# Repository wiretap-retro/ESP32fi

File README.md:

# ESP32fi
A parallel port ESP32 plipbox for the Amiga.

## Info
Do not build. Not tested, firmware and software still pending.

Built for use with the ImpBox32 project: https://github.com/AmigaPorts/ImpBox32

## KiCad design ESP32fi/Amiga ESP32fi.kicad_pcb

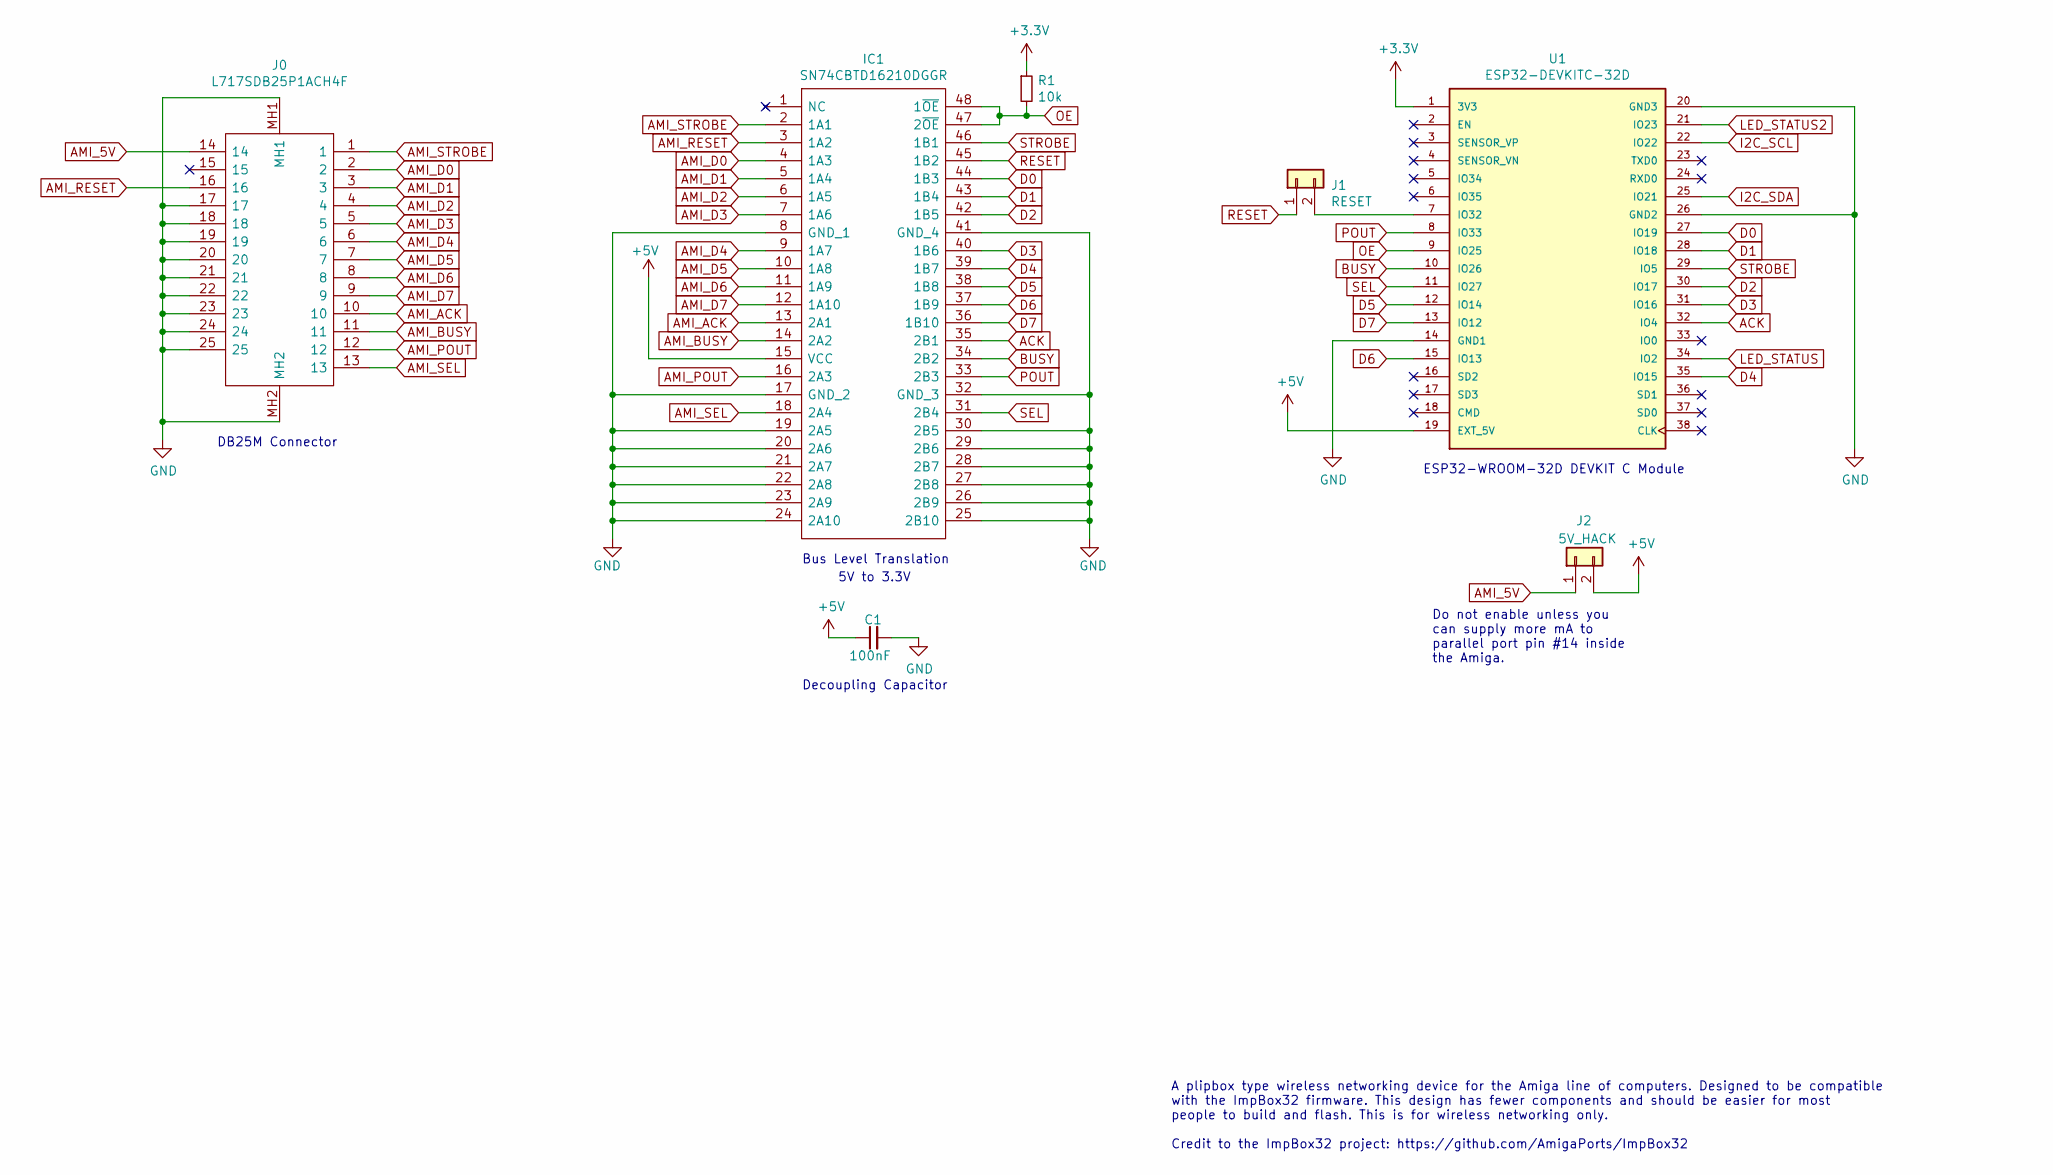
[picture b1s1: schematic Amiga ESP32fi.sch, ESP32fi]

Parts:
C1: 100nF; C_0805_2012Metric_Pad1.15x1.40mm_HandSolder
IC1: SN74CBTD16210DGGR; SOP50P810X120-48N; Mouser Part Number 595-74CBTD16210DGGR
J0: L717SDB25P1ACH4F; Mouser Part Number 523-L717SDB25P1ACH4F
J1: RESET; PinHeader_1x02_P2.54mm_Vertical
J2: 5V_HACK; PinHeader_1x02_P2.54mm_Vertical
R1: 10k; R_0805_2012Metric_Pad1.15x1.40mm_HandSolder
U1: ESP32-DEVKITC-32D; MODULE_ESP32-DEVKITC-32D; PARTREV 4

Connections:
+3V3: R1.1, U1.1 (3V3)
+5V: C1.1, IC1.15 (VCC), J2.2, U1.19 (EXT_5V)
ACK: IC1.35 (2B1), U1.32 (IO4)
AMI_5V: J0.14, J2.1
AMI_ACK: IC1.13 (2A1), J0.10
AMI_BUSY: IC1.14 (2A2), J0.11
AMI_D0: IC1.4 (1A3), J0.2
AMI_D1: IC1.5 (1A4), J0.3
AMI_D2: IC1.6 (1A5), J0.4
AMI_D3: IC1.7 (1A6), J0.5
AMI_D4: IC1.9 (1A7), J0.6
AMI_D5: IC1.10 (1A8), J0.7
AMI_D6: IC1.11 (1A9), J0.8
AMI_D7: IC1.12 (1A10), J0.9
AMI_POUT: IC1.16 (2A3), J0.12
AMI_RESET: IC1.3 (1A2), J0.16
AMI_SEL: IC1.18 (2A4), J0.13
AMI_STROBE: IC1.2 (1A1), J0.1
BUSY: IC1.34 (2B2), U1.10 (IO26)
D0: IC1.44 (1B3), U1.27 (IO19)
D1: IC1.43 (1B4), U1.28 (IO18)
D2: IC1.42 (1B5), U1.30 (IO17)
D3: IC1.40 (1B6), U1.31 (IO16)
D4: IC1.39 (1B7), U1.35 (IO15)
D5: IC1.38 (1B8), U1.12 (IO14)
D6: IC1.37 (1B9), U1.15 (IO13)
D7: IC1.36 (1B10), U1.13 (IO12)
GND: C1.2, IC1.8 (GND_1), IC1.17 (GND_2), IC1.19 (2A5), IC1.20 (2A6), IC1.21 (2A7), IC1.22 (2A8), IC1.23 (2A9), IC1.24 (2A10), IC1.25 (2B10), IC1.26 (2B9), IC1.27 (2B8), IC1.28 (2B7), IC1.29 (2B6), IC1.30 (2B5), IC1.32 (GND_3), IC1.41 (GND_4), J0.17, J0.18, J0.19, J0.20, J0.21, J0.22, J0.23, J0.24, J0.25, J0.MH1, J0.MH2, U1.14 (GND1), U1.20 (GND3), U1.26 (GND2)
I2C_SCL: U1.22 (IO22)
I2C_SDA: U1.25 (IO21)
LED_STATUS: U1.34 (IO2)
LED_STATUS2: U1.21 (IO23)
unnamed: J1.2, U1.7 (IO32)
OE: IC1.47 (2~OE), IC1.48 (1~OE), R1.2, U1.9 (IO25)
POUT: IC1.33 (2B3), U1.8 (IO33)
RESET: IC1.45 (1B2), J1.1
SEL: IC1.31 (2B4), U1.11 (IO27)
STROBE: IC1.46 (1B1), U1.29 (IO5)

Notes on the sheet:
Bus Level Translation
5V to 3.3V
DB25M Connector
ESP32-WROOM-32D DEVKIT C Module
Decoupling Capacitor
Do not enable unless you can supply more mA to parallel port pin #14 inside the Amiga.
A plipbox type wireless networking device for the Amiga line of computers. Designed to be compatible with the ImpBox32 firmware. This design has fewer components and should be easier for most people to build and flash. This is for wireless networking only. Credit to the ImpBox32 project: https://gi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

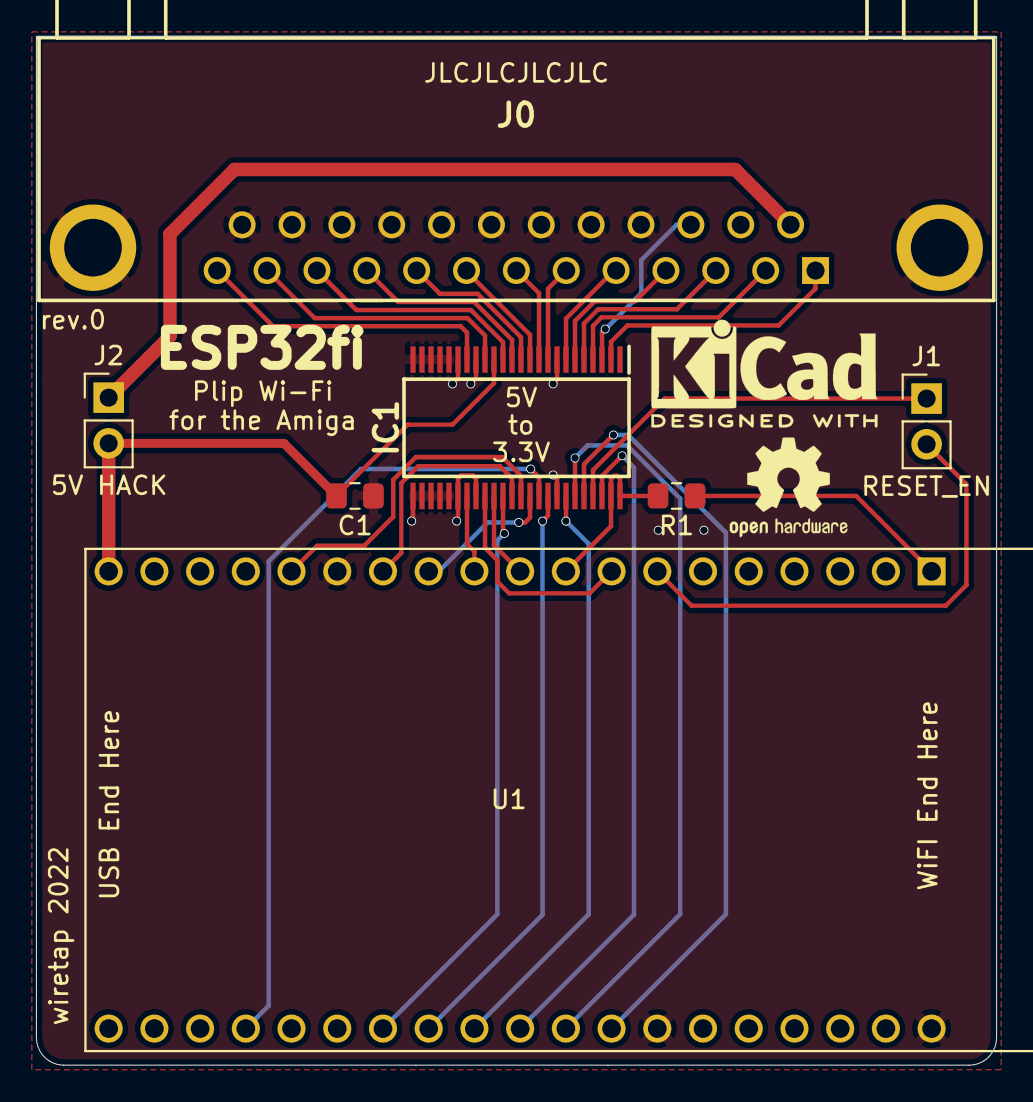
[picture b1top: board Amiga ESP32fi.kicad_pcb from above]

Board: 2 copper layers, 53.3 x 57.2 mm, 7 parts (0 on the bottom side), 34 nets.

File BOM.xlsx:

Reference | Value | Footprint | Description | Manufacturer Name | Manufacturer Part Number
C1 | 100nF | Capacitor_SMD:C_0805_2012Metric_Pad1.15x1.40mm_HandSolder
IC1 | SN74CBTD16210DGGR | SOP50P810X120-48N | SN74CBTD16210DGGR, Bus Switch 74CBT, 10 x 1:1, 4.5 5.5 V 48-Pin TSSOP | Texas Instruments | SN74CBTD16210DGGR
J0 | L717SDB25P1ACH4F | L717SDB25P1ACH4F | Dsub, Stamped Signal 3A, Right Angle PCB Through Hole, FP=10.40mm (0.409in), Ro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 | Amphenol | L717SDB25P1ACH4F
J1 | RESET | Connector_PinHeader_2.54mm:PinHeader_1x02_P2.54mm_Vertical
J2 | 5V_HACK | Connector_PinHeader_2.54mm:PinHeader_1x02_P2.54mm_Vertical
R1 | 10k | Resistor_SMD:R_0805_2012Metric_Pad1.15x1.40mm_HandSolder
U1 | ESP32-DEVKITC-32D | SamacSys_Parts:MODULE_ESP32-DEVKITC-32D |  | HiLetgo | ESP-WROOM-32D Development Board | https://www.amazon.com/HiLetgo-ESP-WROOM-32-Development-Micr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
